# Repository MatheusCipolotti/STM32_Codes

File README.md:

# Códigos:

## STM32F030K6T6:
- [Saída Digital](STM32F030K6T6/Saída_Digital) - Exemplo com a configuração do delay_ms pelo systick
- [Entrada Digital](STM32F030K6T6/Entrada_Digital)
- [Entrada Analógica](STM32F030K6T6/Entrada_Analógica)
- Interrupção Externa (GPIO_EXTI)
- [Interrupção/Estouro do TIM1](STM32F030K6T6/Estouro_TIM1) - Implementação de um contador que utiliza o estouro da incrementação do TIM1
- [PWM](STM32F030K6T6/PWM) - Exemplo utilizando o PWM dos canais CH1, CH1N, CH2, CH2N, CH3 e o CH3N do TIM1
- [UART](STM32F030K6T6/EUSART)
- SPI
    - [Expansão de saídas com o 74HC595](STM32F030K6T6/SPI/Expansão_Saídas)
    - [Expansão de entradas com o 74HC165](STM32F030K6T6/SPI/Expansão_Entradas)
- I2C
- [LCD](STM32F030K6T6/LCD)

## STM32F103C8T6:
- [LCD](STM32F103C8T6/HAL_Library/LCD)

# Placa de testes:
- [STM32F030K6T6](DEV_BOARDS/STM32F030K6T6)

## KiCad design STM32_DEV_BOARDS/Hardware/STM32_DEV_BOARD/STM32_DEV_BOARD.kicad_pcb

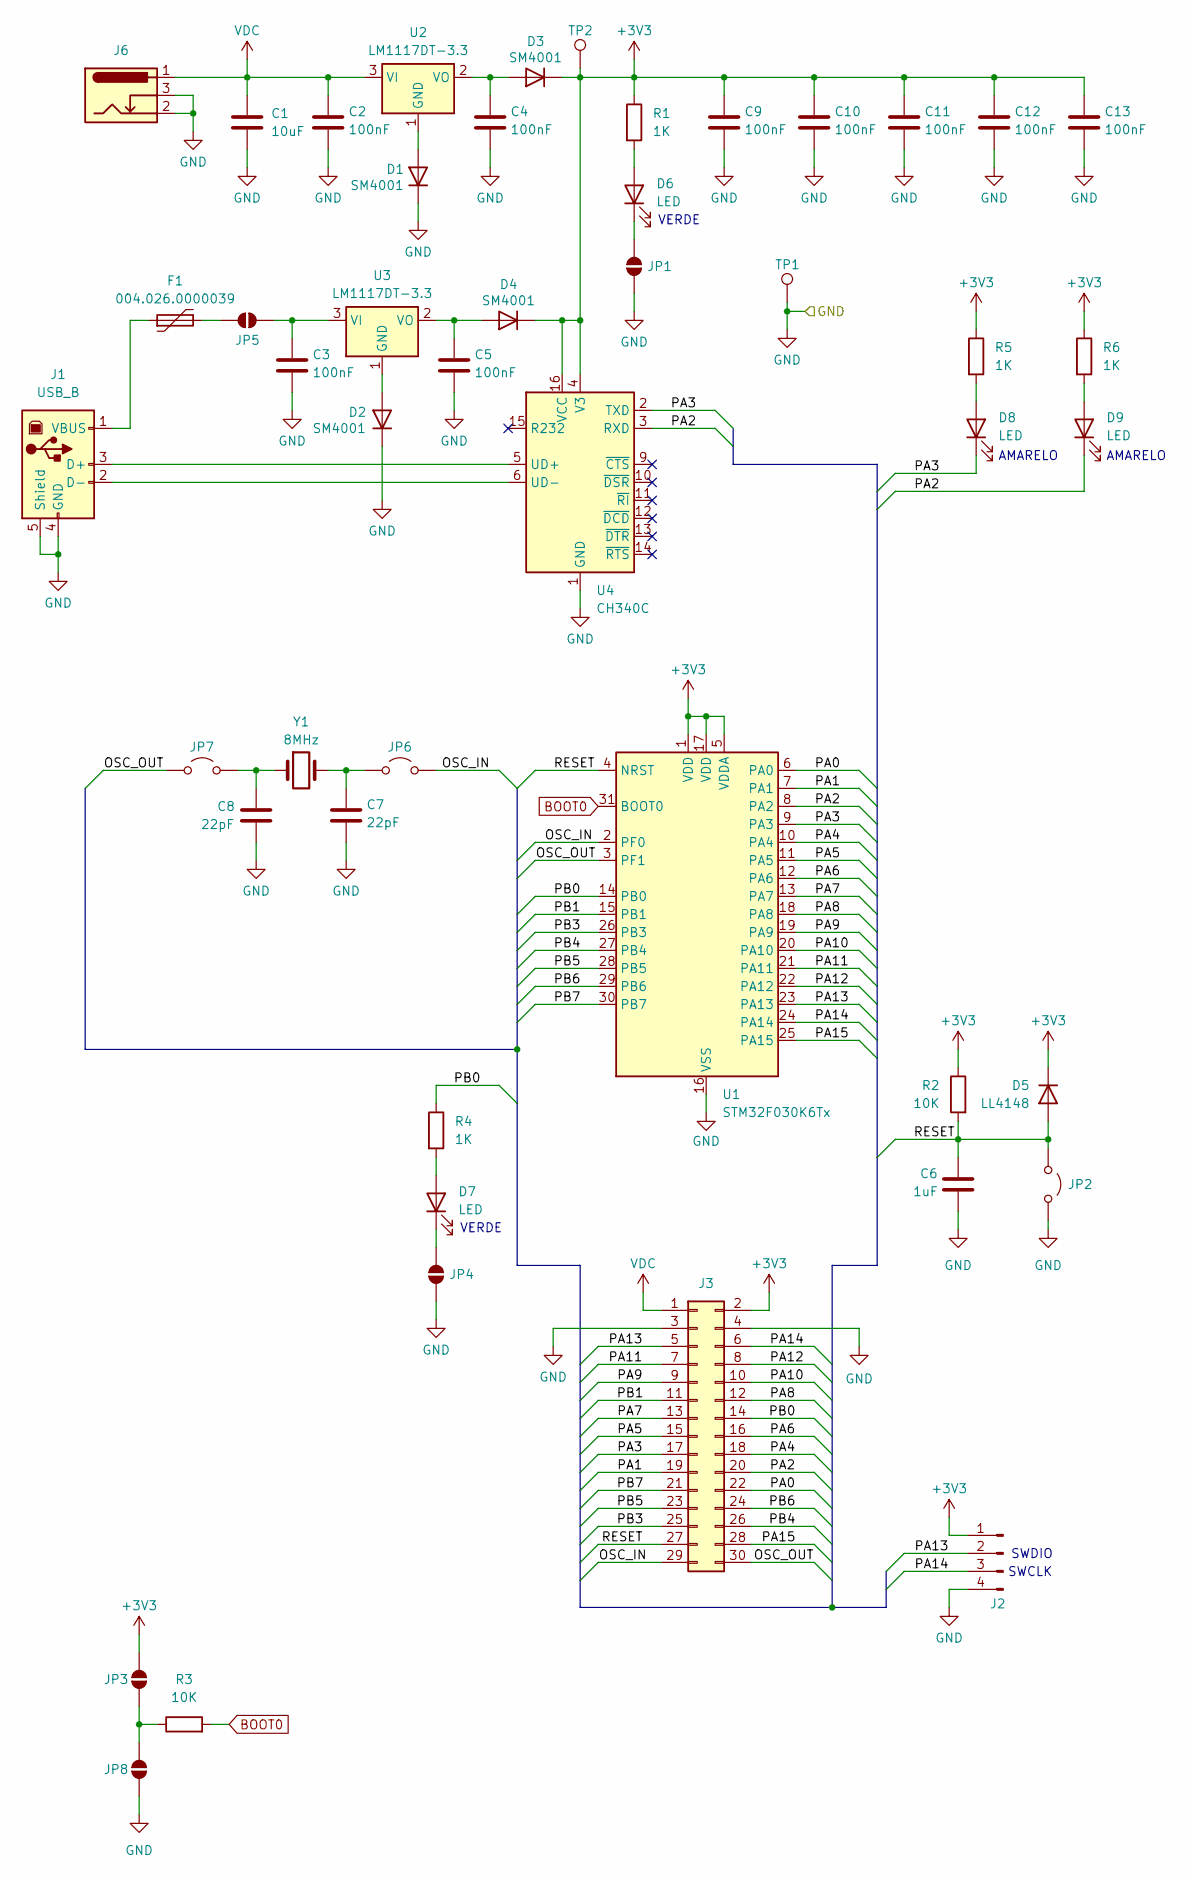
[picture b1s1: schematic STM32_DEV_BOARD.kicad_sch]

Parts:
C1: 10uF; C_1210_3225Metric_Pad1.33x2.70mm_HandSolder
C2, C3, C4, C5, C9, C10, C11, C12, C13: 100nF; C_0805_2012Metric_Pad1.18x1.45mm_HandSolder
C6: 1uF; C_0805_2012Metric_Pad1.18x1.45mm_HandSolder
C7, C8: 22pF; C_0805_2012Metric_Pad1.18x1.45mm_HandSolder
D1, D2, D3, D4: SM4001; D_MELF
D5: LL4148; D_MiniMELF
D6, D7, D8, D9: LED; LED_0805_2012Metric_Pad1.15x1.40mm_HandSolder
F1: 004.026.0000039; Fuse_1206_3216Metric_Pad1.42x1.75mm_HandSolder
J1: USB_B; USB_B_Lumberg_2411_02_Horizontal
J2: Conn_01x04_Pin; PinHeader_1x04_P2.54mm_Vertical
J3: Conn_02x15_Odd_Even; PinHeader_2x15_P2.54mm_Vertical
J6: Barrel_Jack_Switch; BarrelJack_Horizontal
JP1, JP3, JP4, JP5, JP8: SolderJumper_2_Open; SolderJumper-2_P1.3mm_Open_Pad1.0x1.5mm
JP2, JP6, JP7: Jumper_2_Open; TestPoint_2Pads_Pitch2.54mm_Drill0.8mm
R1, R4, R5, R6: 1K; R_0805_2012Metric_Pad1.20x1.40mm_HandSolder
R2, R3: 10K; R_0805_2012Metric_Pad1.20x1.40mm_HandSolder
TP1, TP2: TestPoint_Pad_D1.0mm
U1: STM32F030K6Tx; LQFP-32_7x7mm_P0.8mm
U2, U3: LM1117DT-3.3; TO-252-3_TabPin2
U4: CH340C; SOIC-16_3.9x9.9mm_P1.27mm
Y1: 8MHz; Crystal_HC49-U_Vertical

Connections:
+3V3: C9.1, C10.1, C11.1, C12.1, C13.1, D3.1 (K), D4.1 (K), D5.1 (K), J2.1, J3.2, JP3.1 (A), R1.1, R2.1, R5.1, R6.1, TP2.1, U1.1 (VDD), U1.5 (VDDA), U1.17 (VDD), U4.4 (V3), U4.16 (VCC)
/OSC_IN: J3.29, JP6.2 (B), U1.2 (PF0)
/OSC_OUT: J3.30, JP7.1 (A), U1.3 (PF1)
/PA0: J3.22, U1.6 (PA0)
/PA1: J3.19, U1.7 (PA1)
/PA2: D9.1 (K), J3.20, U1.8 (PA2), U4.3 (RXD)
/PA3: D8.1 (K), J3.17, U1.9 (PA3), U4.2 (TXD)
/PA4: J3.18, U1.10 (PA4)
/PA5: J3.15, U1.11 (PA5)
/PA6: J3.16, U1.12 (PA6)
/PA7: J3.13, U1.13 (PA7)
/PA8: J3.12, U1.18 (PA8)
/PA9: J3.9, U1.19 (PA9)
/PA10: J3.10, U1.20 (PA10)
/PA11: J3.7, U1.21 (PA11)
/PA12: J3.8, U1.22 (PA12)
/PA13: J2.2, J3.5, U1.23 (PA13)
/PA14: J2.3, J3.6, U1.24 (PA14)
/PA15: J3.28, U1.25 (PA15)
/PB0: J3.14, R4.1, U1.14 (PB0)
/PB1: J3.11, U1.15 (PB1)
/PB3: J3.25, U1.26 (PB3)
/PB4: J3.26, U1.27 (PB4)
/PB5: J3.23, U1.28 (PB5)
/PB6: J3.24, U1.29 (PB6)
/PB7: J3.21, U1.30 (PB7)
/RESET: C6.1, D5.2 (A), J3.27, JP2.2 (B), R2.2, U1.4 (NRST)
BOOT0: R3.2, U1.31 (BOOT0)
GND: C1.2, C2.2, C3.2, C4.2, C5.2, C6.2, C7.2, C8.2, C9.2, C10.2, C11.2, C12.2, C13.2, D1.1 (K), D2.1 (K), J1.4 (GND), J1.5 (Shield), J2.4, J3.3, J3.4, J6.2, J6.3, JP1.2 (B), JP2.1 (A), JP4.2 (B), JP8.2 (B), TP1.1, U1.16 (VSS), U1.32 (VSS), U4.1 (GND)
unnamed: D1.2 (A), U2.1 (GND)
unnamed: D2.2 (A), U3.1 (GND)
unnamed: C4.1, D3.2 (A), U2.2 (VO)
unnamed: C5.1, D4.2 (A), U3.2 (VO)
unnamed: D6.2 (A), R1.2
unnamed: D6.1 (K), JP1.1 (A)
unnamed: D7.2 (A), R4.2
unnamed: D7.1 (K), JP4.1 (A)
unnamed: D8.2 (A), R5.2
unnamed: D9.2 (A), R6.2
unnamed: J1.3 (D+), U4.5 (UD+)
unnamed: J1.2 (D-), U4.6 (UD-)
unnamed: F1.1, J1.1 (VBUS)
unnamed: JP3.2 (B), JP8.1 (A), R3.1
unnamed: F1.2, JP5.1 (A)
unnamed: C3.1, JP5.2 (B), U3.3 (VI)
unnamed: C7.1, JP6.1 (A), Y1.2
unnamed: C8.1, JP7.2 (B), Y1.1
VDC: C1.1, C2.1, J3.1, J6.1, U2.3 (VI)

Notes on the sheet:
SWCLK
AMARELO
VERDE
SWDIO

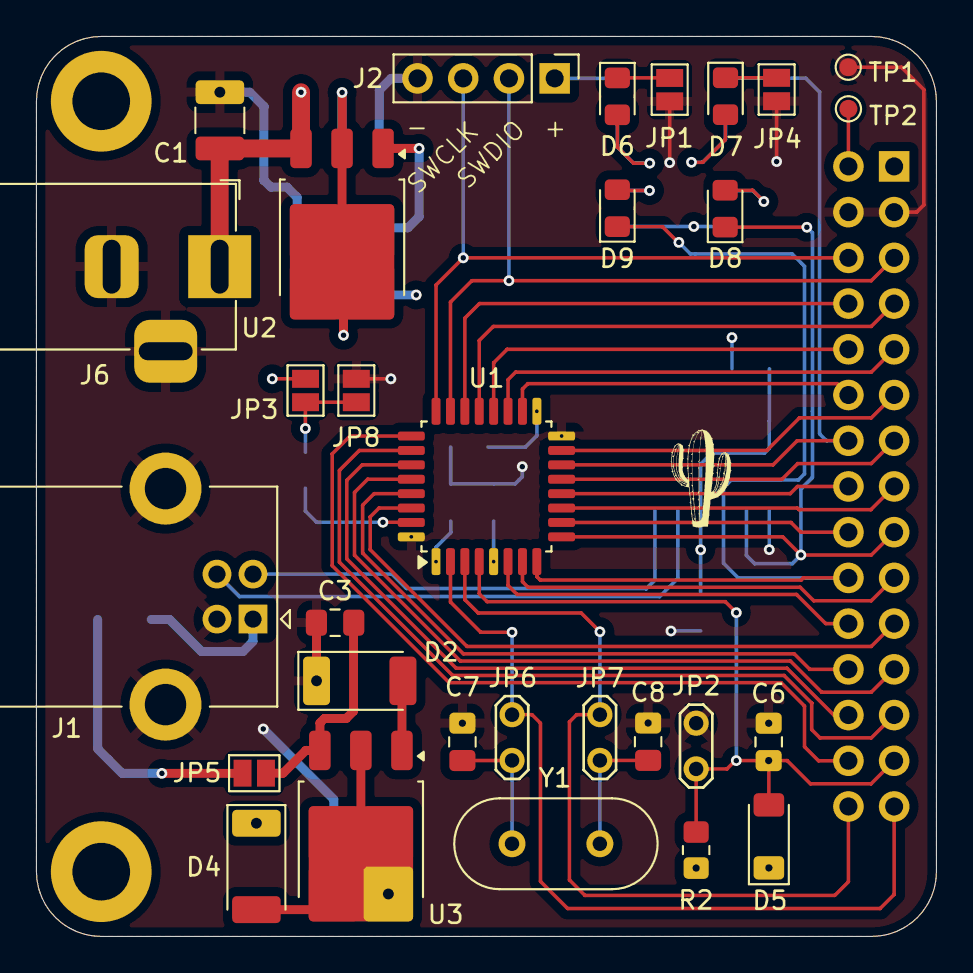
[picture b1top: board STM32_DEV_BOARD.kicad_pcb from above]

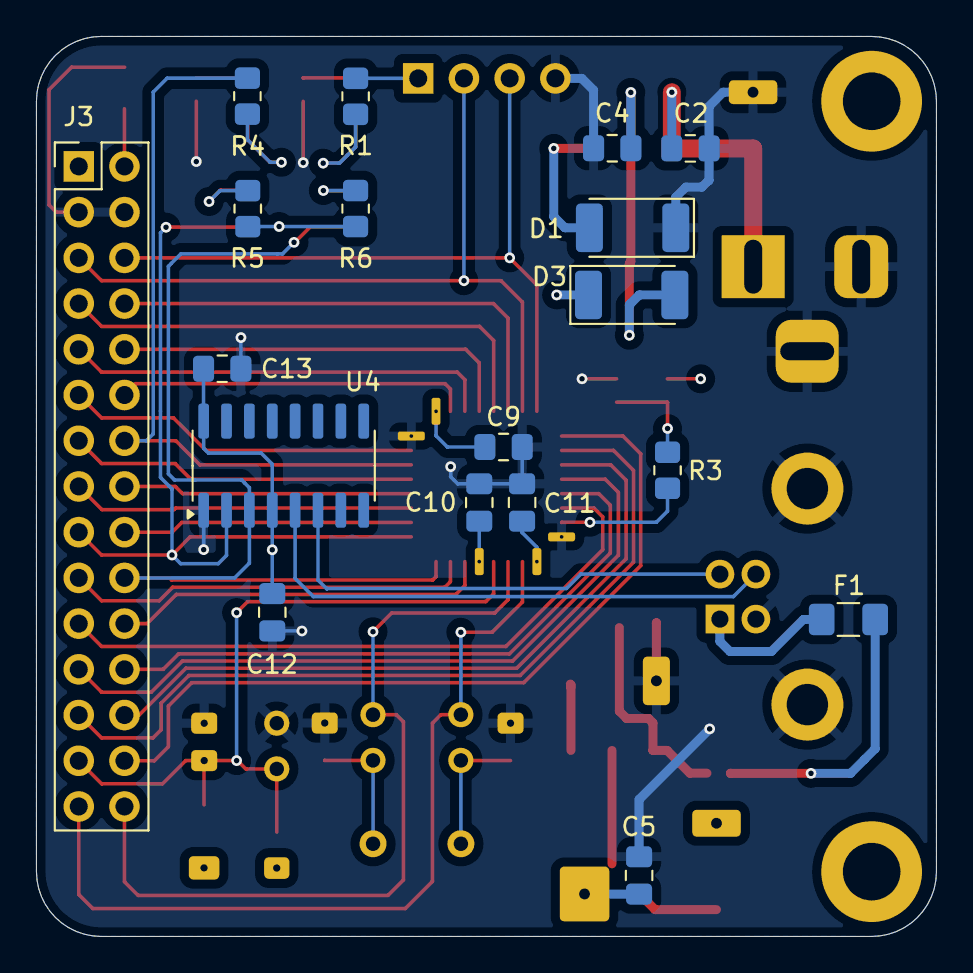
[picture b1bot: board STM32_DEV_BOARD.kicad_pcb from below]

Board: 4 copper layers, 50.0 x 50.0 mm, 48 parts (18 on the bottom side), 48 nets.

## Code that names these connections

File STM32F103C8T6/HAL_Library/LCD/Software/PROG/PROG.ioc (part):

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Mcu.Name=STM32F103C(8-B)Tx
Mcu.Package=LQFP48
Mcu.UserName=STM32F103C8Tx
PB1.Signal=GPIO_Output
PB3.Signal=GPIO_Output
PB4.Signal=GPIO_Output
PB5.Signal=GPIO_Output
PB6.Signal=GPIO_Output
PB7.Signal=GPIO_Output
PD0-OSC_IN.Mode=HSE-External-Oscillator
PD0-OSC_IN.Signal=RCC_OSC_IN
PD1-OSC_OUT.Mode=HSE-External-Oscillator
PD1-OSC_OUT.Signal=RCC_OSC_OUT
RCC.SYSCLKFreq_VALUE=72000000
RCC.SYSCLKSource=RCC_SYSCLKSOURCE_PLLCLK
board=custom

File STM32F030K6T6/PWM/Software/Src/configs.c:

#include "stm32f030x6.h"
#include "configs.h"

void OscInit(void){
	//Ativa o HSE (Cristal Externo de 8 MHz)
	RCC->CR |= RCC_CR_HSEON;
	while (!(RCC->CR & RCC_CR_HSERDY)); 						//Espera até o HSE ficar pronto

	//Seleciona o HSE como o clock do sistema
	RCC->CFGR |= RCC_CFGR_SW_HSE;
	while ((RCC->CFGR & RCC_CFGR_SWS) != RCC_CFGR_SWS_HSE); 			//Espera até o HSE ser selecionado
}

void GPIO(void){
	//Ativa o clock para o GPIOA
	RCC->AHBENR |= RCC_AHBENR_GPIOAEN;

	//Configura o PA7 como saida alternativa para o TIM1_CH1N (AF2)
	GPIOA->MODER &= ~(GPIO_MODER_MODER7);
	GPIOA->MODER |= (GPIO_MODER_MODER7_1); 						//PA7 em modo função alternativa
	GPIOA->AFR[0] |= (0x02 << GPIO_AFRH_AFRH7_Pos); 				//AF2 para PA7

	//Configura o PA8 como saida alternativa para o TIM1_CH1 (AF2)
	GPIOA->MODER &= ~(GPIO_MODER_MODER8);
	GPIOA->MODER |= (GPIO_MODER_MODER8_1); 						//PA8 em modo função alternativa
	GPIOA->AFR[1] |= (0x02 << GPIO_AFRH_AFRH0_Pos); 				//AF2 para PA8

	//Configura o PA9 como saida alternativa para  o TIM1_CH2 (AF2)
	GPIOA->MODER &= ~(GPIO_MODER_MODER9);
	GPIOA->MODER |= (GPIO_MODER_MODER9_1); 						//PA9 em modo função alternativa
	GPIOA->AFR[1] |= (0x02 << GPIO_AFRH_AFRH1_Pos); 				//AF2 para PA9

	//Configura o PA10 como saida alternativa para o TIM1_CH3 (AF2)
	GPIOA->MODER &= ~(GPIO_MODER_MODER10);
	GPIOA->MODER |= (GPIO_MODER_MODER10_1); 					//PA10 em modo função alternativa
	GPIOA->AFR[1] |= (0x02 << GPIO_AFRH_AFRH2_Pos); 				//AF2 para PA10

	//Ativa o clock para o GPIOB
	RCC->AHBENR |= RCC_AHBENR_GPIOBEN;

	//Configura o PB0 como saida alternativa para o TIM1_CH2N (AF2)
	GPIOB->MODER &= ~(GPIO_MODER_MODER0);
	GPIOB->MODER |= (GPIO_MODER_MODER0_1); 						//PB0 em modo função alternativa
	GPIOB->AFR[0] |= (0x02 << GPIO_AFRH_AFRH0_Pos); 				//AF2 para PB0

	//Configura o PB1 como saida alternativa para o TIM1_CH3N (AF2)
	GPIOB->MODER &= ~(GPIO_MODER_MODER1);
	GPIOB->MODER |= (GPIO_MODER_MODER1_1); 						//PB1 em modo função alternativa
	GPIOB->AFR[0] |= (0x02 << GPIO_AFRH_AFRH1_Pos); 				//AF2 para PB1	
}

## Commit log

2024-10-18 STM32F030K6T6_DEV_BOARD
2024-10-18 Blink
2024-10-18 CMSIS
